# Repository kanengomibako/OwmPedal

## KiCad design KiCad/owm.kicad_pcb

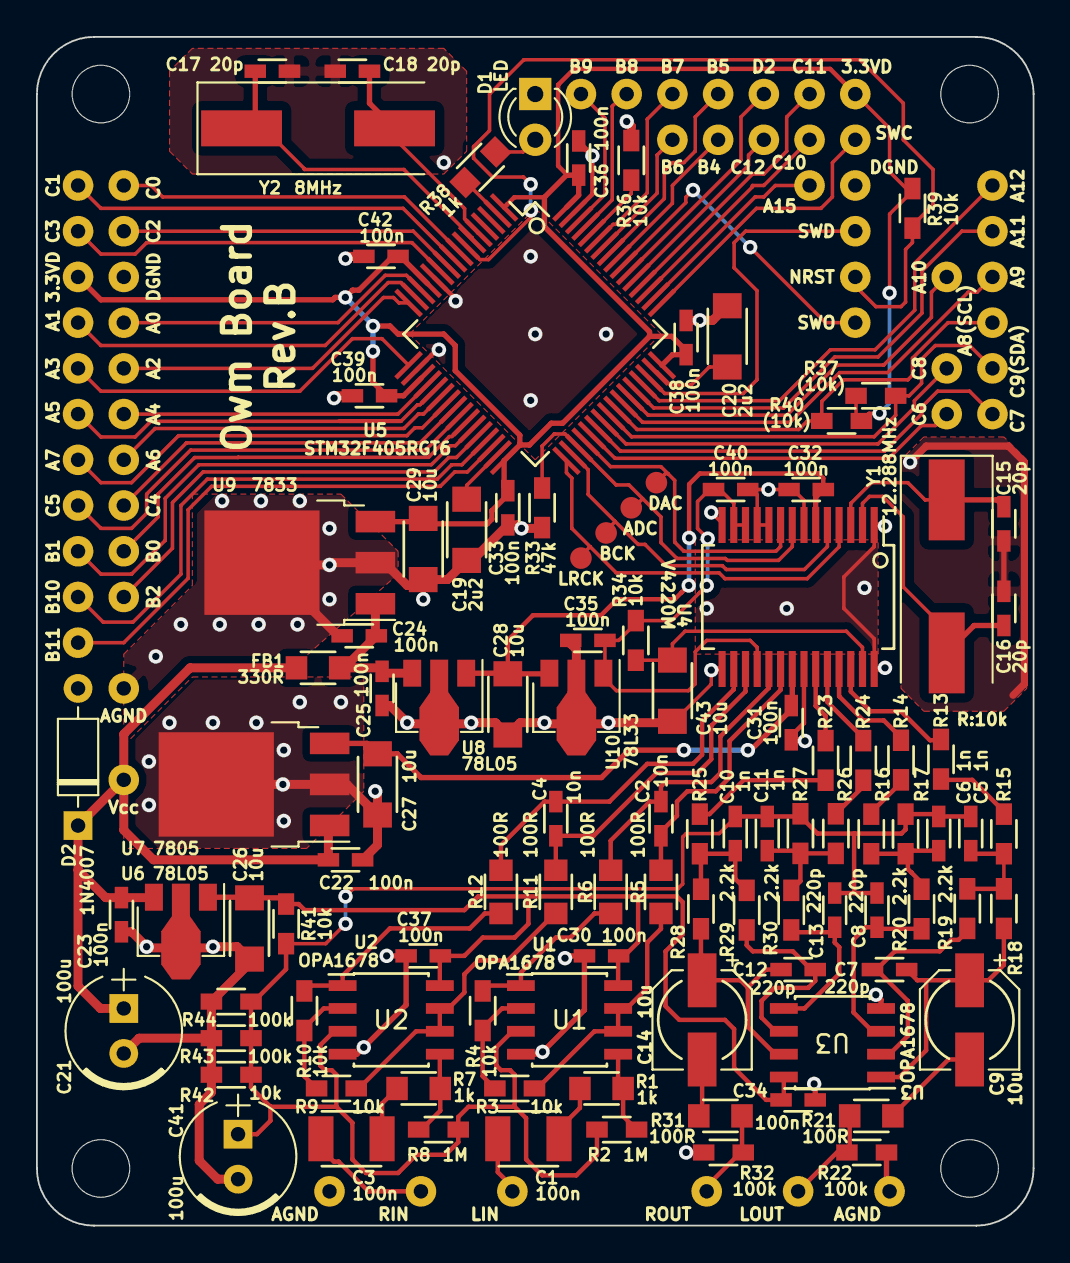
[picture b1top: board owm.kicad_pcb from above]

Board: 2 copper layers, 55.4 x 66.0 mm, 160 parts (0 on the bottom side), 104 nets.

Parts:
C1, C3: 100n; my_C_3225(1210)_HandSoldering
C2, C4: 10n; my_C_1608(0603)_HandSoldering
C5, C6, C10, C11: 1n; my_C_1608(0603)_HandSoldering
C7, C8, C12, C13: 220p; my_C_1608(0603)_HandSoldering
C9, C14: 10u; my_CP_Elec_5
C15, C16, C17, C18: 20p; my_C_1608(0603)_HandSoldering
C19, C20: 2u2; my_C_3216(1206)_HandSoldering
C21, C41: 100u; my_C_D6.3mm_P2.50mm
C22, C23, C24, C25, C30, C31, C32, C33, C34, C35, C36, C37, C38, C39, C40, C42: 100n; my_C_1608(0603)_HandSoldering
C26, C27, C28, C29, C43: 10u; my_C_3216(1206)_HandSoldering
D1: LED; LED_D3.0mm
D2: 1N4007; D_DO-35_SOD27_P7.62mm_Horizontal
FB1: 330R; my_R_2012(0805)_HandSoldering
J1: LIN; my_SmallPad_0-8mmDrill
J2: RIN; my_SmallPad_0-8mmDrill
J3: LOUT; my_SmallPad_0-8mmDrill
J4: ROUT; my_SmallPad_0-8mmDrill
J5: C9(SDA); my_SmallPad_0-8mmDrill
J6: D2; my_SmallPad_0-8mmDrill
J7: C0; my_SmallPad_0-8mmDrill
J8: C1; my_SmallPad_0-8mmDrill
J9: C2; my_SmallPad_0-8mmDrill
J10: C3; my_SmallPad_0-8mmDrill
J11: C4; my_SmallPad_0-8mmDrill
J12: C5; my_SmallPad_0-8mmDrill
J13: C6; my_SmallPad_0-8mmDrill
J14: C7; my_SmallPad_0-8mmDrill
J15: C8; my_SmallPad_0-8mmDrill
J16: C11; my_SmallPad_0-8mmDrill
J17, J18: 3.3VD; my_SmallPad_0-8mmDrill
J19, J20: DGND; my_SmallPad_0-8mmDrill
J21: A0; my_SmallPad_0-8mmDrill
J22: A1; my_SmallPad_0-8mmDrill
J23: A2; my_SmallPad_0-8mmDrill
J24: A3; my_SmallPad_0-8mmDrill
J25: A4; my_SmallPad_0-8mmDrill
J26: A5; my_SmallPad_0-8mmDrill
J27: A6; my_SmallPad_0-8mmDrill
J28: A7; my_SmallPad_0-8mmDrill
J29: A9; my_SmallPad_0-8mmDrill
J30: A10; my_SmallPad_0-8mmDrill
J31: A11; my_SmallPad_0-8mmDrill
J32: A12; my_SmallPad_0-8mmDrill
J33: SWD; my_SmallPad_0-8mmDrill
J34: SWC; my_SmallPad_0-8mmDrill
J35: B0; my_SmallPad_0-8mmDrill
J36: B1; my_SmallPad_0-8mmDrill
J37: B2; my_SmallPad_0-8mmDrill
J38: SWO; my_SmallPad_0-8mmDrill
J39: B4; my_SmallPad_0-8mmDrill
J40: B5; my_SmallPad_0-8mmDrill
J41: B6; my_SmallPad_0-8mmDrill
J42: B7; my_SmallPad_0-8mmDrill
J43: B8; my_SmallPad_0-8mmDrill
J44: B9; my_SmallPad_0-8mmDrill
J45: B10; my_SmallPad_0-8mmDrill
J46: B11; my_SmallPad_0-8mmDrill
J47: A15; my_SmallPad_0-8mmDrill
J48: A8(SCL); my_SmallPad_0-8mmDrill
J49, J51, J52: AGND; my_SmallPad_0-8mmDrill
J50: Vcc; my_SmallPad_0-8mmDrill
J53: NRST; my_SmallPad_0-8mmDrill
J54: C10; my_SmallPad_0-8mmDrill
J55: C12; my_SmallPad_0-8mmDrill
R1, R7, R38: 1k; my_R_2012(0805)_HandSoldering
R2, R8: 1M; my_R_1608(0603)_HandSoldering
R3, R4, R9, R10, R13, R14, R15, R16, R17, R18, R23, R24, R25, R26, R27, R28, R34, R36, R39, R41, R42: 10k; my_R_1608(0603)_HandSoldering
R5, R6, R11, R12, R21, R31: 100R; my_R_2012(0805)_HandSoldering
R19, R20, R29, R30: 2.2k; my_R_1608(0603)_HandSoldering
R22, R32, R43, R44: 100k; my_R_1608(0603)_HandSoldering
R33: 47k; my_R_1608(0603)_HandSoldering
R37, R40: (10k); my_R_1608(0603)_HandSoldering
TP1: ADC; my_TestPoint_1.2mm
TP2: LRCK; my_TestPoint_1.2mm
TP3: BCK; my_TestPoint_1.2mm
TP4: DAC; my_TestPoint_1.2mm
U1, U2, U3: OPA1678; SOIC-8_3.9x4.9mm_P1.27mm
U4: V4220M; my_SSOP-28_5.3x10.2mm_Pitch0.65mm
U5: STM32F405RGT6; my_LQFP-64_10x10_P0.5
U6, U8: 78L05; SOT-89-3
U7: 7805; TO-252-3_TabPin2
U9: 7833; TO-252-3_TabPin2
U10: 78L33; SOT-89-3
Y1: 12.288MHz; Crystal_SMD_HC49-SD
Y2: 8MHz; Crystal_SMD_HC49-SD

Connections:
+3V3: C29.1, C33.1, C36.1, C38.1, C39.1, C42.1, J17.1, J18.1, R37.1, R39.1, R40.1, U5.1, U5.13, U5.19, U5.32, U5.48, U5.64, U9.3
+5VA: C27.1, C31.1, U4.21, U7.3
+5VD: C28.1, C32.1, U4.6, U8.1, U10.3
+9V: C21.1, C22.1, C23.1, D2.1, FB1.2, J50.1, U6.3, U7.1
/+3.3VL: C35.1, C40.1, R34.1, U4.12, U4.13, U4.18, U10.1
/+5VAA: C26.1, C30.1, C34.1, C37.1, R41.2, U1.8, U2.8, U3.8, U6.1
/ADCDATA: R33.1, TP1.1, U4.8, U5.35
/BCK: TP3.1, U4.5, U5.34
/BIAS: C5.2, C6.2, C8.2, C10.2, C11.2, C13.2, C41.1, R2.2, R8.2, R17.2, R27.2, R41.1, R42.1, R43.1, R44.1, U1.3, U2.3
/DACDATA: TP4.1, U4.9, U5.36
/LADC+: C2.1, R5.1, U4.20
/LADC-: C2.2, R6.1, U4.19
/LDAC+: R14.2, U4.25
/LDAC-: R13.2, U4.26
/LRCK: TP2.1, U4.4, U5.33
/RADC+: C4.1, R11.1, U4.17
/RADC-: C4.2, R12.1, U4.16
/RDAC+: R24.2, U4.24
/RDAC-: R23.2, U4.23
GNDA: C15.2, C16.2, C17.2, C18.2, C19.2, C20.2, C21.2, C22.2, C23.2, C24.2, C25.2, C26.2, C27.2, C28.2, C29.2, C30.2, C31.2, C32.2, C33.2, C34.2, C35.2, C36.2, C37.2, C38.2, C39.2, C40.2, C41.2, C42.2, C43.2, D1.1, D2.2, J19.1, J20.1, J49.1, J51.1, J52.1, R22.2, R32.2, R33.2, R36.2, R42.2, R43.2, R44.2, U1.4, U2.4, U3.4, U4.1, U4.7, U4.10, U4.11, U4.14, U4.15, U4.22, U4.28, U5.12, U5.18, U5.63, U6.2, U7.2, U8.2, U9.2, U10.2
unnamed: C1.1, R1.2
unnamed: C1.2, J1.1
unnamed: C3.1, R7.2
unnamed: C3.2, J2.1
unnamed: C5.1, R15.1, R18.2, R19.2
unnamed: C6.1, R16.1, R17.1, R20.2
unnamed: C7.1, C9.1, R18.1, U3.1
unnamed: C7.2, R19.1, U3.2
unnamed: C8.1, R20.1, U3.3
unnamed: C9.2, R21.2
unnamed: C10.1, R25.1, R28.2, R29.2
unnamed: C11.1, R26.1, R27.1, R30.2
unnamed: C12.1, C14.1, R28.1, U3.7
unnamed: C12.2, R29.1, U3.6
unnamed: C13.1, R30.1, U3.5
unnamed: C14.2, R31.2
unnamed: C15.1, U4.3, Y1.1
unnamed: C16.1, U4.2, Y1.2
unnamed: C17.1, U5.6, Y2.1
unnamed: C18.1, U5.5, Y2.2
unnamed: C19.1, U5.31
unnamed: C20.1, U5.47
unnamed: C24.1, C25.1, FB1.1, U8.3, U9.1
unnamed: C43.1, R34.2, U4.27
unnamed: D1.2, R38.1
unnamed: J3.1, R21.1, R22.1
unnamed: J4.1, R31.1, R32.1
unnamed: J5.1, R37.2, U5.40
unnamed: J6.1, U5.54
unnamed: J7.1, U5.8
unnamed: J8.1, U5.9
unnamed: J9.1, U5.10
unnamed: J10.1, U5.11
unnamed: J11.1, U5.24
unnamed: J12.1, U5.25
unnamed: J13.1, U5.37
unnamed: J14.1, U5.38
unnamed: J15.1, U5.39
unnamed: J16.1, U5.52
unnamed: J21.1, U5.14
unnamed: J22.1, U5.15
unnamed: J23.1, U5.16
unnamed: J24.1, U5.17
unnamed: J25.1, U5.20
unnamed: J26.1, U5.21
unnamed: J27.1, U5.22
unnamed: J28.1, U5.23
unnamed: J29.1, U5.42
unnamed: J30.1, U5.43
unnamed: J31.1, U5.44
unnamed: J32.1, U5.45
unnamed: J33.1, U5.46
unnamed: J34.1, U5.49
unnamed: J35.1, U5.26
unnamed: J36.1, U5.27
unnamed: J37.1, U5.28
unnamed: J38.1, U5.55
unnamed: J39.1, U5.56
unnamed: J40.1, U5.57
unnamed: J41.1, U5.58
unnamed: J42.1, U5.59
unnamed: J43.1, U5.61
unnamed: J44.1, U5.62
unnamed: J45.1, U5.29
unnamed: J46.1, U5.30
unnamed: J47.1, U5.50
unnamed: J48.1, R40.2, U5.41
unnamed: J53.1, R39.2, U5.7
unnamed: J54.1, U5.51
unnamed: J55.1, U5.53
unnamed: R1.1, R2.1, U1.5
unnamed: R3.1, R5.2, U1.6, U1.7
unnamed: R3.2, R4.2, U1.2
unnamed: R4.1, R6.2, U1.1
unnamed: R7.1, R8.1, U2.5
unnamed: R10.1, R12.2, U2.1
unnamed: R9.2, R10.2, U2.2
unnamed: R9.1, R11.2, U2.6, U2.7
unnamed: R13.1, R15.2
unnamed: R14.1, R16.2
unnamed: R23.1, R25.2
unnamed: R24.1, R26.2
unnamed: R36.1, U5.60
unnamed: R38.2, U5.2

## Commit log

2019-02-06 Create owm.txt
    c
2019-03-04 Source追加
2019-03-07 Priority変更
2019-03-19 CubeMX5.1.0
2019-03-19 Update stm32f4xx_hal_i2s_ex.c
    HAL_I2SEx_TxRxCpltCallbackが起きない不具合を修正
2019-03-22 Update main.c
    HAL_I2SEx_TxRxCpltCallbackを追加し処理方法を変更
2019-03-29 I2Sを32ビットへ変更
2019-04-22 Create LICENSE
